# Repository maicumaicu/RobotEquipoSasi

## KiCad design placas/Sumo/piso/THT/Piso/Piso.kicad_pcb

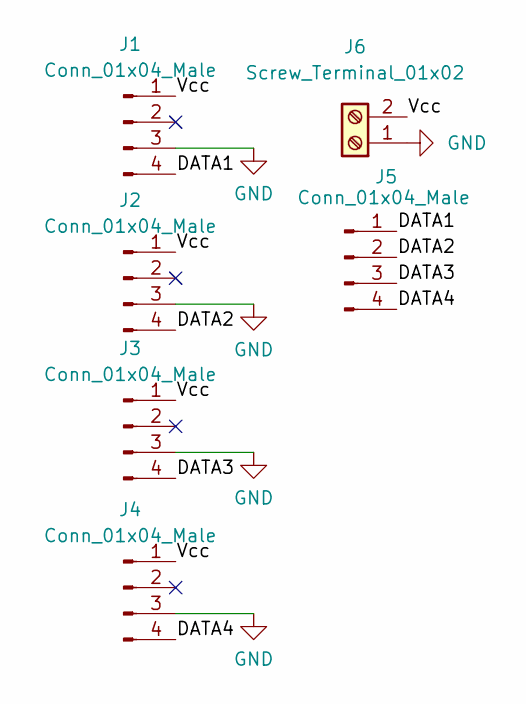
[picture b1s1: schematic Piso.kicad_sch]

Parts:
J1, J2, J3, J4, J5: Conn_01x04_Male; PinHeader_1x04_P2.54mm_Horizontal
J6: Screw_Terminal_01x02; TerminalBlock_bornier-2_P5.08mm

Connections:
/DATA1: J1.4, J5.1
/DATA2: J2.4, J5.2
/DATA3: J3.4, J5.3
/DATA4: J4.4, J5.4
/Vcc: J1.1, J2.1, J3.1, J4.1, J6.2
GND: J1.3, J2.3, J3.3, J4.3, J6.1

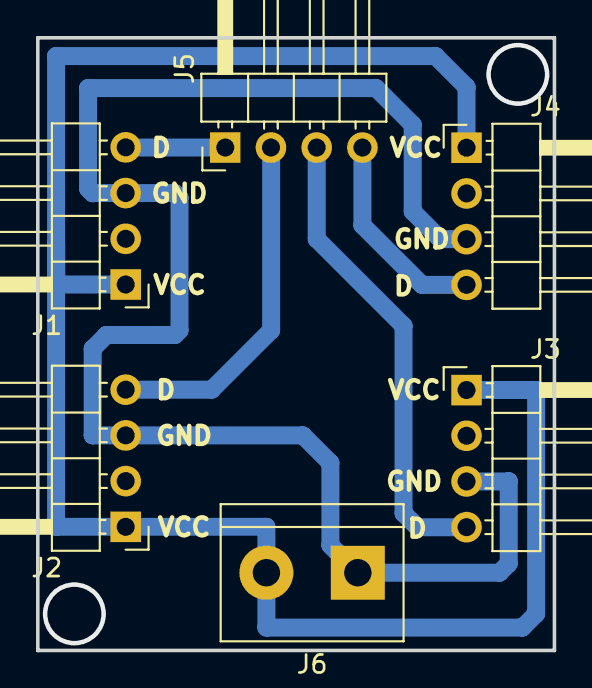
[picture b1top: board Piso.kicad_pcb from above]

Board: 2 copper layers, 28.7 x 34.0 mm, 6 parts (0 on the bottom side), 6 nets.

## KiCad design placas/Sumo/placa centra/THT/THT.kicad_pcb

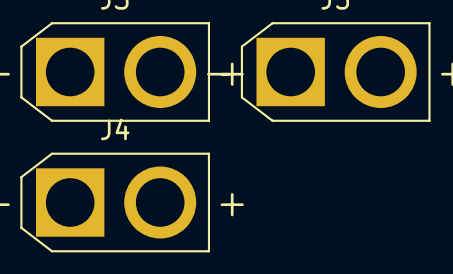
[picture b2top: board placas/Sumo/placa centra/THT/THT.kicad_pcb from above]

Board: 2 copper layers, 3 parts (0 on the bottom side), 2 nets, no tracks yet.

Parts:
J3: BATERIA; AMASS_XT30U-F_1x02_P5.0mm_Vertical
J4: MOTORES; AMASS_XT30U-F_1x02_P5.0mm_Vertical
J5: SENSORES; AMASS_XT30U-F_1x02_P5.0mm_Vertical

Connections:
/GND: J3.1, J4.1, J5.1
/VCC: J3.2, J4.2, J5.2

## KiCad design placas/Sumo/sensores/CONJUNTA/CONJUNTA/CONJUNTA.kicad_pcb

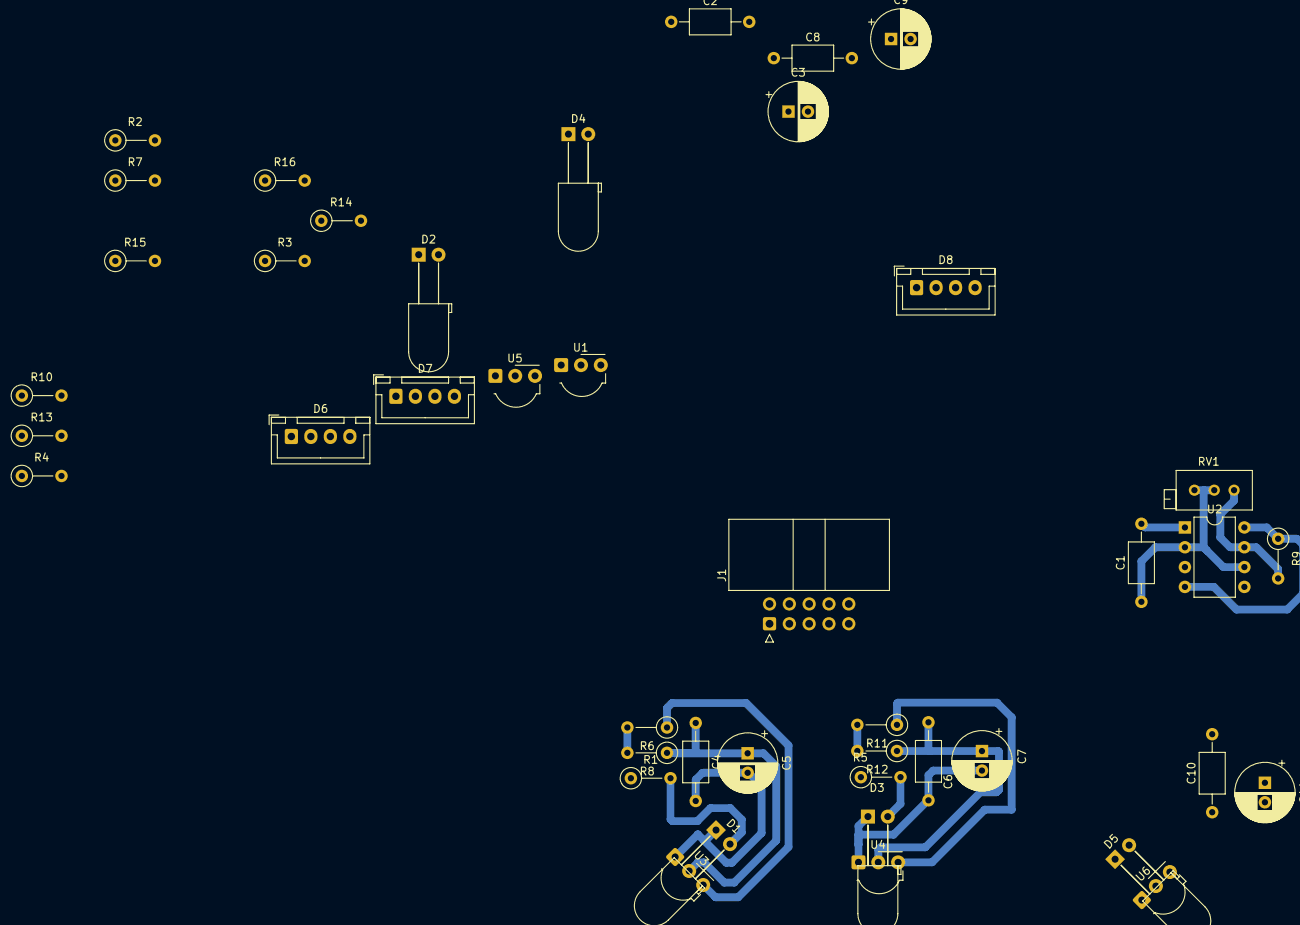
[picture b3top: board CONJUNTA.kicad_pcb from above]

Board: 2 copper layers, 43 parts (0 on the bottom side), 24 nets.

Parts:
C1, C2, C4, C6, C8, C10: 102; C_Axial_L5.1mm_D3.1mm_P10.00mm_Horizontal
C3, C5, C7, C9, C11: 104; CP_Radial_D7.5mm_P2.50mm
D1, D2, D3, D4, D5: LED; LED_D5.0mm_Horizontal_O6.35mm_Z3.0mm
D6, D7, D8: Conn_01x04_Male; JST_XH_B4B-XH-A_1x04_P2.50mm_Vertical
J1: Control Sensores; IDC-Header_2x05_P2.54mm_Horizontal
R1, R4, R5, R7, R10: 220; R_Axial_DIN0207_L6.3mm_D2.5mm_P5.08mm_Vertical
R2, R6, R11, R13, R15: 20k; R_Axial_DIN0207_L6.3mm_D2.5mm_P5.08mm_Vertical
R3, R8, R12, R14, R16: 100; R_Axial_DIN0207_L6.3mm_D2.5mm_P5.08mm_Vertical
R9: 1k8; R_Axial_DIN0207_L6.3mm_D2.5mm_P5.08mm_Vertical
RV1: R_Potentiometer; Potentiometer_Bourns_3296X_Horizontal
U1, U3, U4, U5, U6: TSOP17xx; Vishay_MOLD-3Pin
U2: LM555xN; DIP-8_W7.62mm

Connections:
/5v: D6.4, D7.4, D8.4, J1.1, R2.2, R3.2, R6.2, R8.2, R9.1, R11.2, R12.2, R13.2, R14.2, R15.2, R16.2, U2.4 (R), U2.8 (VCC)
/S1: J1.9, R15.1, U6.3 (OUT)
/S2: J1.7, R13.1, U5.3 (OUT)
/S3: J1.5, R11.1, U4.3 (OUT)
/S4: J1.3, R6.1, U3.3 (OUT)
/S5: J1.10, R2.1, U1.3 (OUT)
/S6: D6.3, J1.8
/S7: D7.3, J1.6
/S8: D8.3, J1.4
/gnd: D6.2, D7.2, D8.2
GND: C1.2, C2.2, C3.2, C4.2, C5.2, C6.2, C7.2, C8.2, C9.2, C10.2, C11.2, D1.1 (K), D2.1 (K), D3.1 (K), D4.1 (K), D5.1 (K), J1.2, U1.1 (GND), U2.1 (GND), U3.1 (GND), U4.1 (GND), U5.1 (GND), U6.1 (GND)
unnamed: C1.1, RV1.2, RV1.3, U2.2 (TR), U2.6 (THR)
unnamed: C2.1, C3.1, R3.1, U1.2 (Vs)
unnamed: C4.1, C5.1, R8.1, U3.2 (Vs)
unnamed: C6.1, C7.1, R12.1, U4.2 (Vs)
unnamed: C8.1, C9.1, R14.1, U5.2 (Vs)
unnamed: C10.1, C11.1, R16.1, U6.2 (Vs)
unnamed: D1.2 (A), R1.2
unnamed: D2.2 (A), R4.2
unnamed: D3.2 (A), R5.2
unnamed: D4.2 (A), R7.2
unnamed: D5.2 (A), R10.2
unnamed: D6.1, D7.1, D8.1, R1.1, R4.1, R5.1, R7.1, R10.1, U2.3 (Q)
unnamed: R9.2, RV1.1, U2.7 (DIS)

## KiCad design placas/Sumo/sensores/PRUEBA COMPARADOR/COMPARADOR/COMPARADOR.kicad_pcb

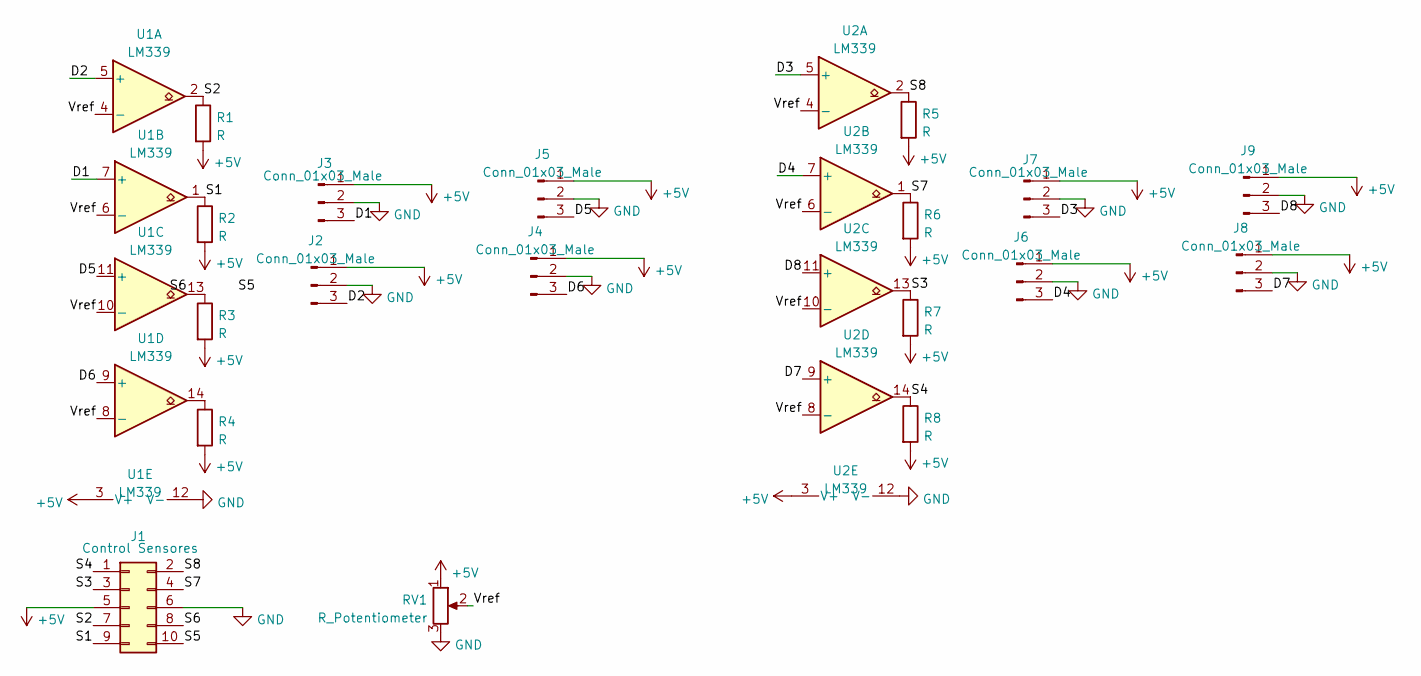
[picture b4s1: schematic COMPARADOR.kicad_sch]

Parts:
J1: Control Sensores; IDC-Header_2x05_P2.54mm_Horizontal
J2, J3, J4, J5, J6, J7, J8, J9: Conn_01x03_Male; PinHeader_1x03_P2.54mm_Vertical
R1, R2, R3, R4, R5, R6, R7, R8: R; R_Axial_DIN0207_L6.3mm_D2.5mm_P10.16mm_Horizontal
RV1: R_Potentiometer; Potentiometer_Bourns_3299W_Vertical
U1, U2: LM339; DIP-14_W7.62mm_Socket_LongPads

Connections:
+5V: J1.5, J2.1, J3.1, J4.1, J5.1, J6.1, J7.1, J8.1, J9.1, R1.2, R2.2, R3.2, R4.2, R5.2, R6.2, R7.2, R8.2, RV1.1, U1.3 (V+), U2.3 (V+)
/D1: J3.3, U1.7 (+)
/D2: J2.3, U1.5 (+)
/D3: J7.3, U2.5 (+)
/D4: J6.3, U2.7 (+)
/D5: J5.3, U1.11 (+)
/D6: J4.3, U1.9 (+)
/D7: J8.3, U2.9 (+)
/D8: J9.3, U2.11 (+)
/S1: J1.9, R2.1, U1.1
/S2: J1.7, R1.1, U1.2
/S3: J1.3, R7.1, U2.13
/S4: J1.1, R8.1, U2.14
/S5: J1.10
/S6: J1.8
/S7: J1.4, R6.1, U2.1
/S8: J1.2, R5.1, U2.2
/Vref: RV1.2, U1.4 (-), U1.6 (-), U1.8 (-), U1.10 (-), U2.4 (-), U2.6 (-), U2.8 (-), U2.10 (-)
GND: J1.6, J2.2, J3.2, J4.2, J5.2, J6.2, J7.2, J8.2, J9.2, RV1.3, U1.12 (V-), U2.12 (V-)
unnamed: R3.1, U1.13
unnamed: R4.1, U1.14

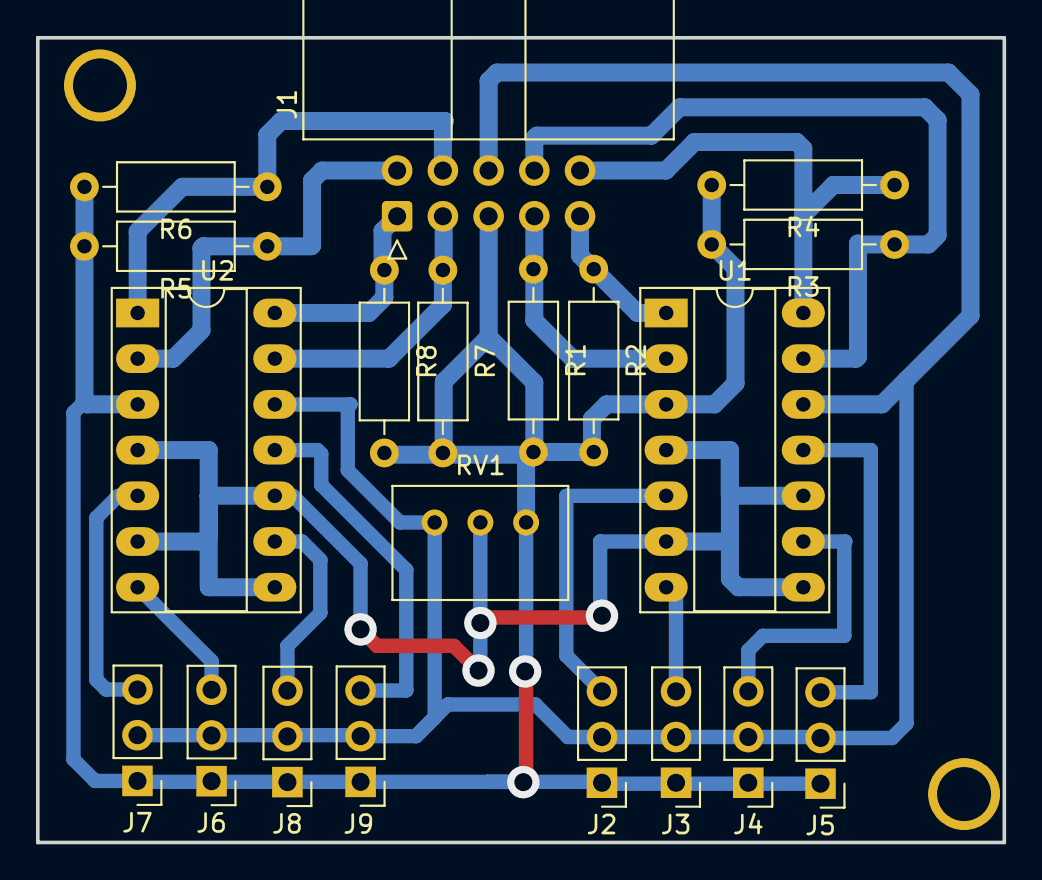
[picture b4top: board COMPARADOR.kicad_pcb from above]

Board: 2 copper layers, 53.7 x 44.7 mm, 20 parts (0 on the bottom side), 19 nets.

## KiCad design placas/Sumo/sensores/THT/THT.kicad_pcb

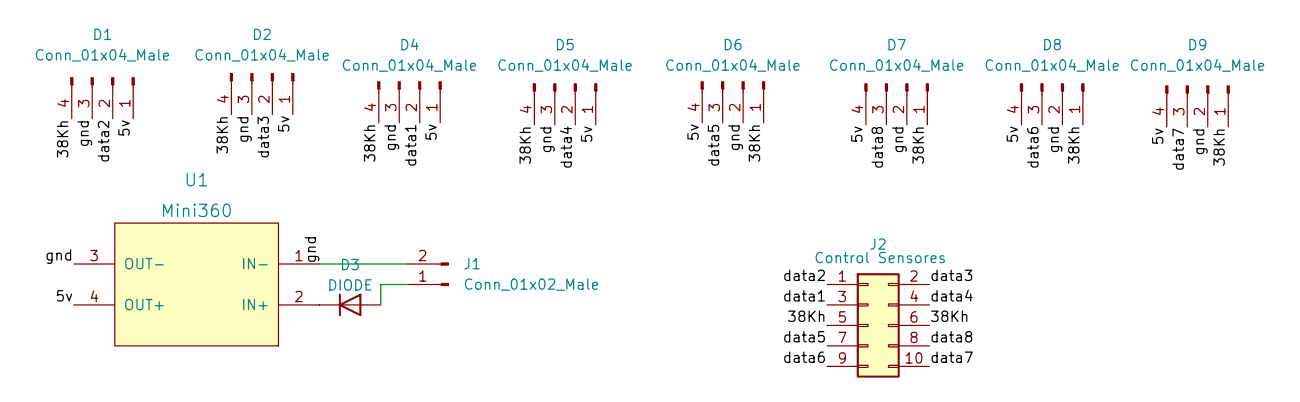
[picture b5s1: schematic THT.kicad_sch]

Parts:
D1, D2, D4, D5, D6, D7, D8, D9: Conn_01x04_Male; PinHeader_1x04_P2.54mm_Horizontal
D3: DIODE; D_5W_P12.70mm_Horizontal
J1: Conn_01x02_Male; TerminalBlock_bornier-2_P5.08mm
J2: Control Sensores; IDC-Header_2x05_P2.54mm_Vertical
U1: Mini360; Mini360_step-down

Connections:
/5v: D1.1, D2.1, D4.1, D5.1, D6.4, D7.4, D8.4, D9.4, U1.4 (OUT+)
/38Kh: D1.4, D2.4, D4.4, D5.4, D6.1, D7.1, D8.1, D9.1, J2.5, J2.6
/data1: D4.2, J2.3
/data2: D1.2, J2.1
/data3: D2.2, J2.2
/data4: D5.2, J2.4
/data5: D6.3, J2.7
/data6: D8.3, J2.9
/data7: D9.3, J2.10
/data8: D7.3, J2.8
/gnd: D1.3, D2.3, D4.3, D5.3, D6.2, D7.2, D8.2, D9.2, J1.2, U1.1 (IN-), U1.3 (OUT-)
unnamed: D3.1 (A), J1.1
unnamed: D3.2 (K), U1.2 (IN+)

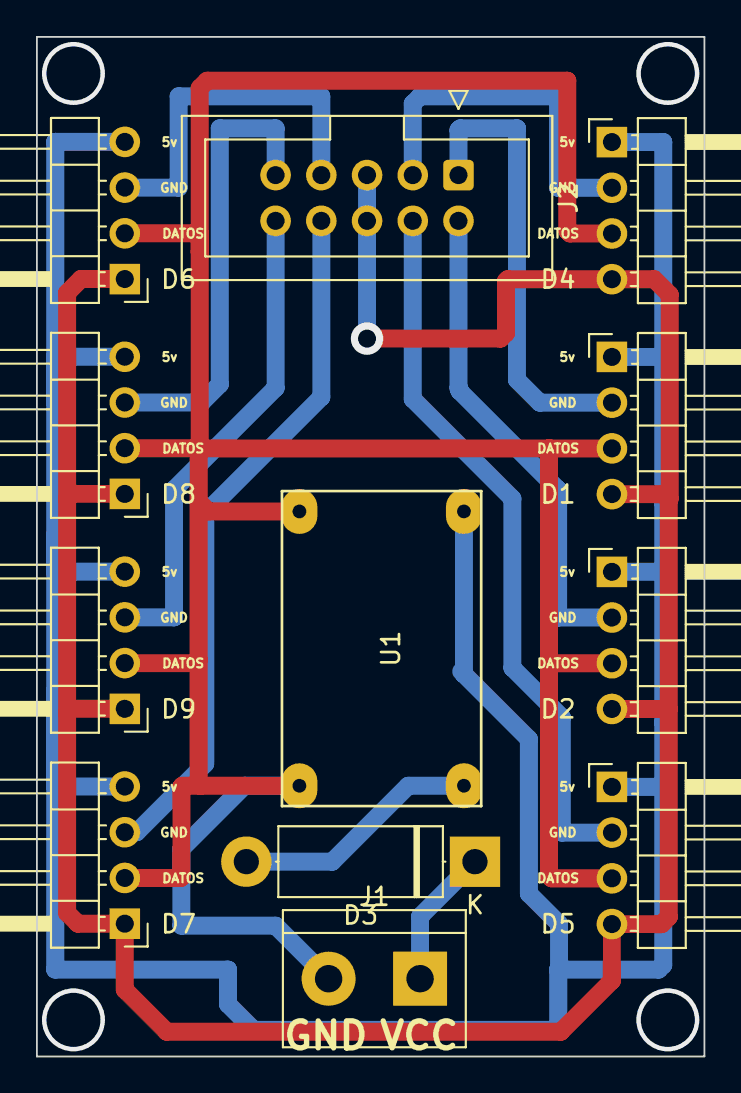
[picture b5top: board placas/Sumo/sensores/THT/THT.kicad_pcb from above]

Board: 2 copper layers, 37.1 x 56.6 mm, 12 parts (0 on the bottom side), 13 nets.

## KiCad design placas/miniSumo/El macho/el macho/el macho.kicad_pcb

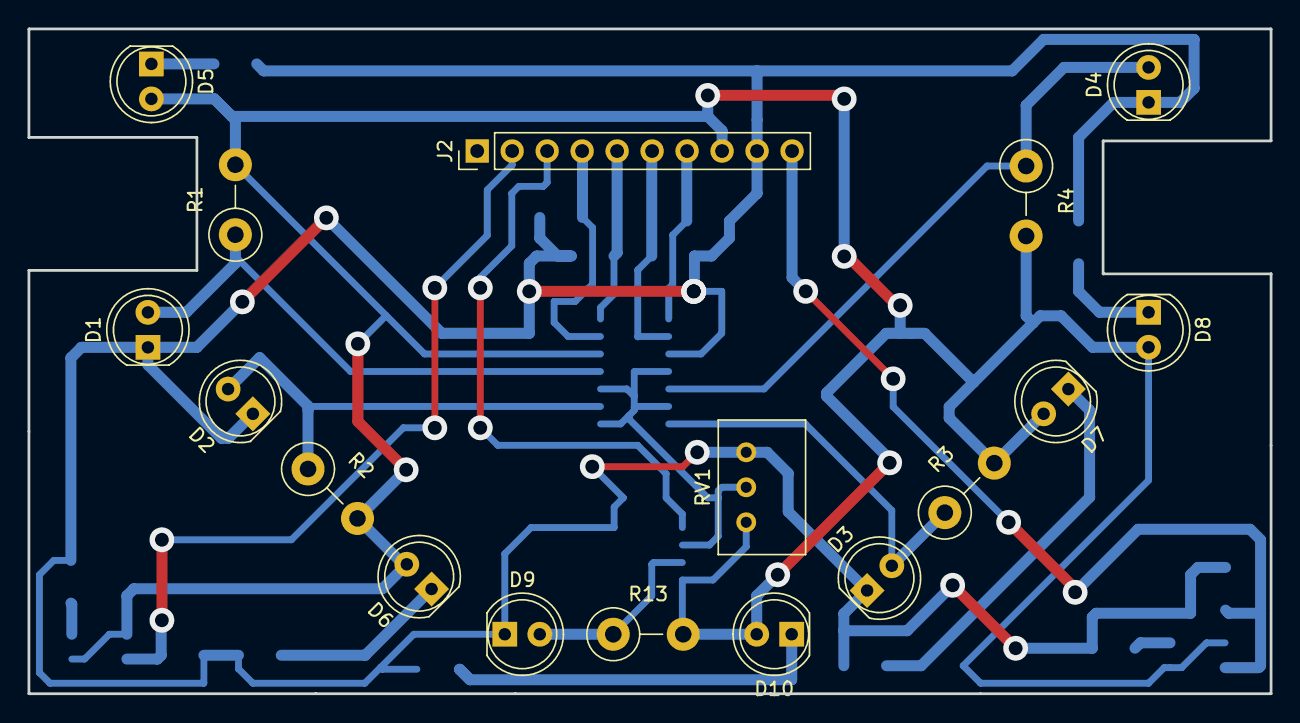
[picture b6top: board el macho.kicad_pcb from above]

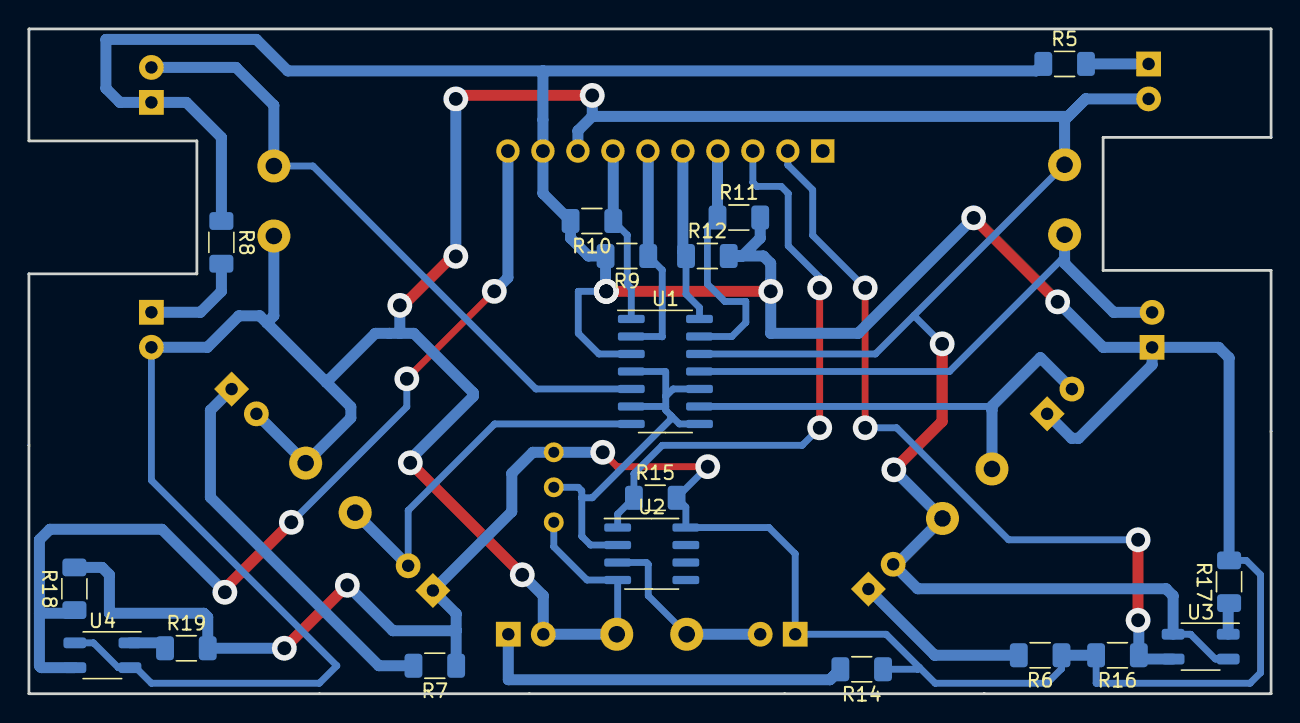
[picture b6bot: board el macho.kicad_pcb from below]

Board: 2 copper layers, 90.2 x 48.3 mm, 35 parts (18 on the bottom side), 22 nets.

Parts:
D1, D2, D3, D4, D9: IR RECEIVER; LED_D5.0mm
D5, D6, D7, D8, D10: IR TRANSMITTER; LED_D5.0mm
J2: Conn_01x10_Pin; PinHeader_1x10_P2.54mm_Vertical
R1, R2, R3, R4, R13: 10k; R_Axial_DIN0411_L9.9mm_D3.6mm_P5.08mm_Vertical
R5, R6, R7, R8, R14: 100; R_1206_3216Metric_Pad1.30x1.75mm_HandSolder
R9, R10, R11, R12, R15: 1k; R_1206_3216Metric_Pad1.30x1.75mm_HandSolder
R16, R18: 47K; R_1206_3216Metric_Pad1.30x1.75mm_HandSolder
R17, R19: 22; R_1206_3216Metric_Pad1.30x1.75mm_HandSolder
RV1: R_Potentiometer; Potentiometer_Bourns_3299W_Vertical
U1: LM339; SO-14_3.9x8.65mm_P1.27mm
U2: LM358; SOIC-8_3.9x4.9mm_P1.27mm
U3, U4: QRE1113GR; OnSemi_CASE100CY

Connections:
+5V: D1.1 (K), D2.1 (K), D3.1 (K), D4.1 (K), D9.1 (K), J2.9, R5.1, R6.1, R7.1, R8.1, R9.2, R10.2, R11.2, R12.2, R14.1, R15.2, R16.2, R17.2, R18.2, R19.2, RV1.1, U1.3 (V+), U2.8 (V+)
/D1: D4.2 (A), R4.1, U1.5 (+)
/D2: D3.2 (A), R3.1, U1.7 (+)
/D3: D2.2 (A), R2.1, U1.9 (+)
/D4: D1.2 (A), R1.1, U1.11 (+)
/D5: D9.2 (A), R13.1, U2.3 (+)
/SIGNAL1: J2.2, R16.1, U3.3
/SIGNAL2: J2.10, R18.1, U4.3
GND: D5.2 (A), D6.2 (A), D7.2 (A), D8.2 (A), D10.2 (A), J2.8, R1.2, R2.2, R3.2, R4.2, R13.2, RV1.3, U1.12 (V-), U2.4 (V-), U3.2 (K), U3.4, U4.2 (K), U4.4
unnamed: D5.1 (K), R5.2
unnamed: D6.1 (K), R6.2
unnamed: D7.1 (K), R7.2
unnamed: D8.1 (K), R8.2
unnamed: D10.1 (K), R14.2
unnamed: J2.3, R15.1, U2.1
unnamed: J2.4, R11.1, U1.13
unnamed: J2.5, R12.1, U1.14
unnamed: J2.6, R9.1, U1.2
unnamed: J2.7, R10.1, U1.1
unnamed: RV1.2, U1.4 (-), U1.6 (-), U1.8 (-), U1.10 (-), U2.2 (-)
unnamed: R17.1, U3.1 (A)
unnamed: R19.1, U4.1 (A)

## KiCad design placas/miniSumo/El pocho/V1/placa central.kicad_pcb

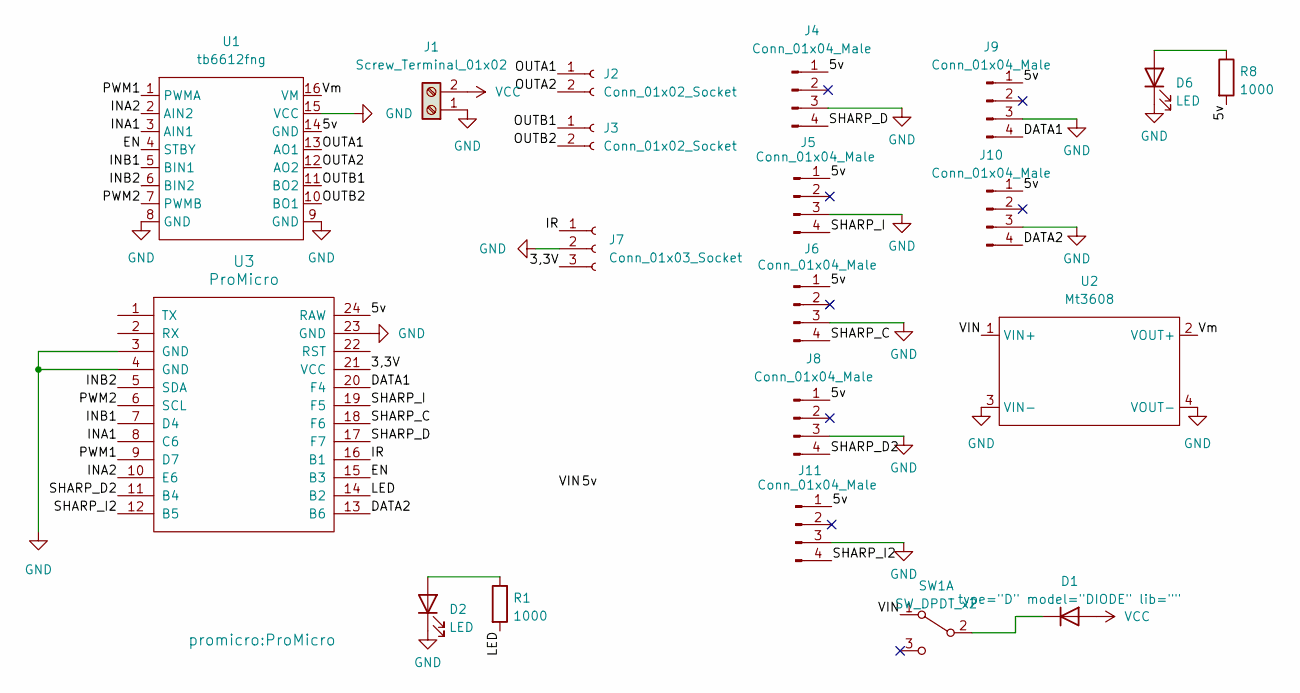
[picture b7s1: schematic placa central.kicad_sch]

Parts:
D1: type="D" model="DIODE" lib=""; D_5W_P5.08mm_Vertical_AnodeUp
D2, D6: LED; LED_D3.0mm_FlatTop
J1: Screw_Terminal_01x02; PinSocket_1x02_P2.54mm_Vertical
J2, J3: Conn_01x02_Socket; PinSocket_1x02_P2.54mm_Vertical
J4, J5, J6, J8, J9, J10, J11: Conn_01x04_Male; PinHeader_1x04_P2.54mm_Vertical
J7: Conn_01x03_Socket; PinSocket_1x03_P2.54mm_Vertical
R1, R8: 1000; R_1210_3225Metric
SW1: SW_DPDT_x2; SW_Slide_1P2T_CK_OS102011MS2Q
U1: tb6612fng
U2: Mt3608; Sx1308
U3: ProMicro

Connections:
/3,3V: J7.3, U3.21 (VCC)
/5v: J4.1, J5.1, J6.1, J8.1, J9.1, J10.1, J11.1, R8.2, SW1.1 (A), U1.14 (GND), U2.1 (VIN+), U3.24 (RAW)
/DATA1: J9.4, U3.20 (F4)
/DATA2: J10.4, U3.13 (B6)
/EN: U1.4 (STBY), U3.15 (B3)
/INA1: U1.3 (AIN1), U3.8 (C6)
/INA2: U1.2 (AIN2), U3.10 (E6)
/INB1: U1.5 (BIN1), U3.7 (D4)
/INB2: U1.6 (BIN2), U3.5 (SDA)
/IR: J7.1, U3.16 (B1)
/LED: R1.2, U3.14 (B2)
/OUTA1: J2.1, U1.13 (AO1)
/OUTA2: J2.2, U1.12 (AO2)
/OUTB1: J3.1, U1.11 (BO2)
/OUTB2: J3.2, U1.10 (BO1)
/PWM1: U1.1 (PWMA), U3.9 (D7)
/PWM2: U1.7 (PWMB), U3.6 (SCL)
/SHARP_C: J6.4, U3.18 (F6)
/SHARP_D: J4.4, U3.17 (F7)
/SHARP_D2: J8.4, U3.11 (B4)
/SHARP_I: J5.4, U3.19 (F5)
/SHARP_I2: J11.4, U3.12 (B5)
/Vm: U1.16 (VM), U2.2 (VOUT+)
GND: D2.1 (K), D6.1 (K), J1.1, J4.3, J5.3, J6.3, J7.2, J8.3, J9.3, J10.3, J11.3, U1.8 (GND), U1.9 (GND), U1.15 (VCC), U2.3 (VIN-), U2.4 (VOUT-), U3.3 (GND), U3.4 (GND), U3.23 (GND)
unnamed: D1.2 (K), SW1.2 (B)
unnamed: D2.2 (A), R1.1
unnamed: D6.2 (A), R8.1
VCC: D1.1 (A), J1.2

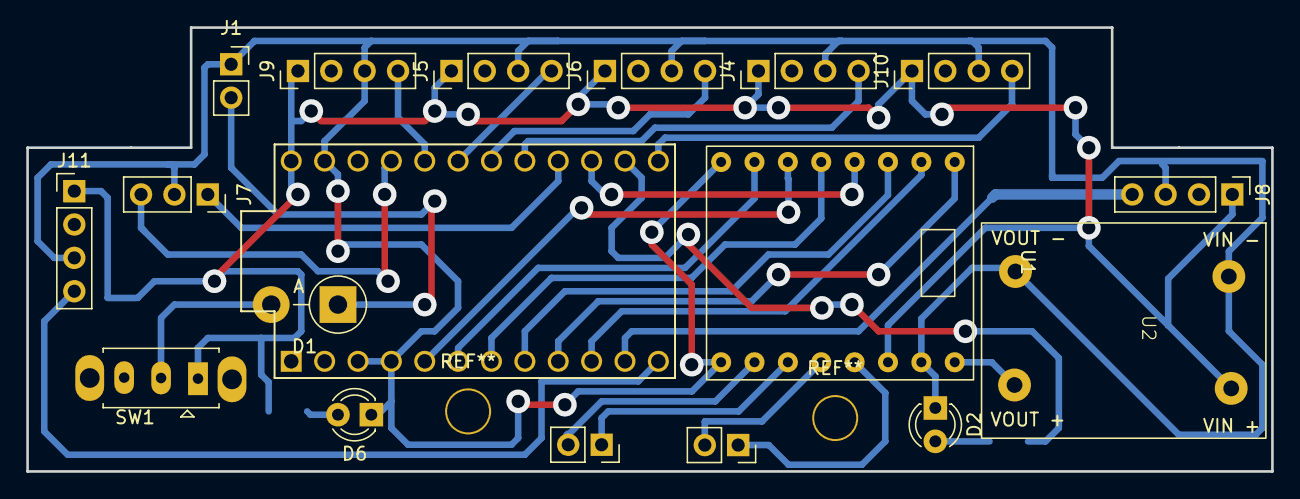
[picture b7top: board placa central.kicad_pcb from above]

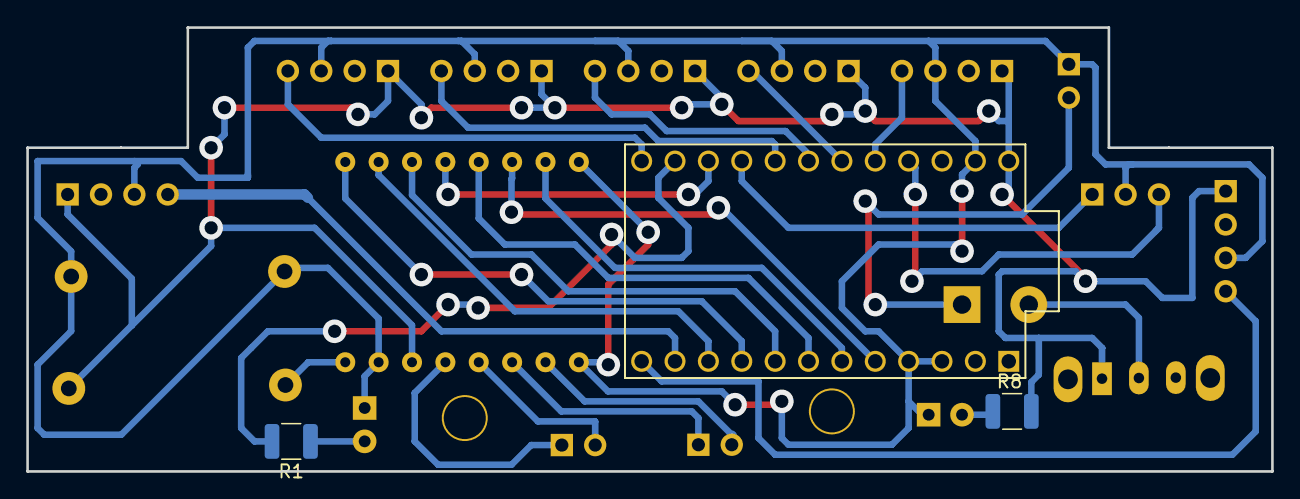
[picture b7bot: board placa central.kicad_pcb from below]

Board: 2 copper layers, 94.7 x 33.8 mm, 20 parts (2 on the bottom side), 28 nets.

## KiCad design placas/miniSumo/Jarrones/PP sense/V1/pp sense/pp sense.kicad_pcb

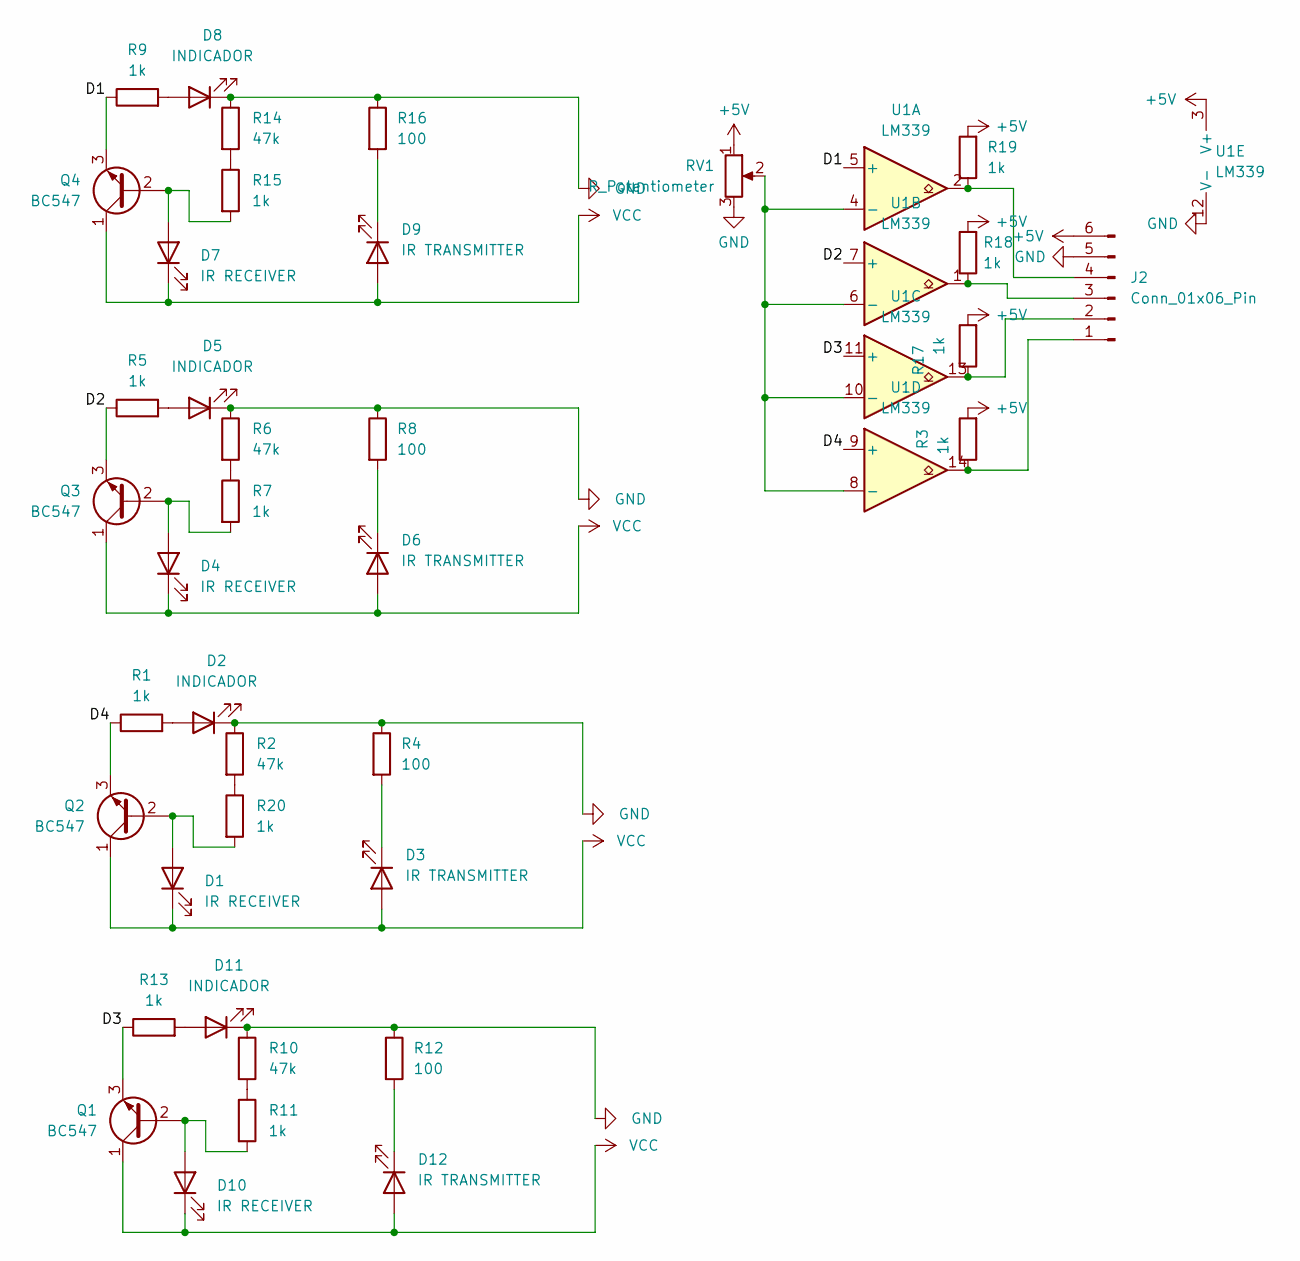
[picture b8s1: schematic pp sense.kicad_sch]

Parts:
D1, D4, D7, D10: IR RECEIVER; LED_D5.0mm
D2, D5, D8, D11: INDICADOR; LED_1206_3216Metric_Pad1.42x1.75mm_HandSolder
D3, D6, D9, D12: IR TRANSMITTER; LED_D5.0mm
J2: Conn_01x06_Pin; PinHeader_1x06_P2.54mm_Vertical
Q1, Q2, Q3, Q4: BC547; TO-92_Inline
R1, R3, R5, R7, R9, R11, R13, R15, R17, R18, R19, R20: 1k; R_1206_3216Metric_Pad1.30x1.75mm_HandSolder
R2, R6, R10, R14: 47k; R_1206_3216Metric_Pad1.30x1.75mm_HandSolder
R4, R8, R12, R16: 100; R_1206_3216Metric_Pad1.30x1.75mm_HandSolder
RV1: R_Potentiometer; Potentiometer_Bourns_3299W_Vertical
U1: LM339; DIP-14_W7.62mm

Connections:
+5V: J2.6, R3.2, R17.2, R18.2, R19.2, RV1.1, U1.3 (V+)
/D1: Q4.3 (E), R9.1, U1.5 (+)
/D2: Q3.3 (E), R5.1, U1.7 (+)
/D3: Q1.3 (E), R13.1, U1.11 (+)
/D4: Q2.3 (E), R1.1, U1.9 (+)
GND: D2.1 (K), D5.1 (K), D8.1 (K), D11.1 (K), J2.5, R2.1, R4.1, R6.1, R8.1, R10.1, R12.1, R14.1, R16.1, RV1.3, U1.12 (V-)
unnamed: D1.2 (A), Q2.2 (B), R20.2
unnamed: D2.2 (A), R1.2
unnamed: D3.1 (K), R4.2
unnamed: D4.2 (A), Q3.2 (B), R7.2
unnamed: D5.2 (A), R5.2
unnamed: D6.1 (K), R8.2
unnamed: D7.2 (A), Q4.2 (B), R15.2
unnamed: D8.2 (A), R9.2
unnamed: D9.1 (K), R16.2
unnamed: D10.2 (A), Q1.2 (B), R11.2
unnamed: D11.2 (A), R13.2
unnamed: D12.1 (K), R12.2
unnamed: J2.1, R3.1, U1.14
unnamed: J2.2, R17.1, U1.13
unnamed: J2.3, R18.1, U1.1
unnamed: J2.4, R19.1, U1.2
unnamed: R2.2, R20.1
unnamed: R6.2, R7.1
unnamed: R10.2, R11.1
unnamed: R14.2, R15.1
unnamed: RV1.2, U1.4 (-), U1.6 (-), U1.8 (-), U1.10 (-)
VCC: D1.1 (K), D3.2 (A), D4.1 (K), D6.2 (A), D7.1 (K), D9.2 (A), D10.1 (K), D12.2 (A), Q1.1 (C), Q2.1 (C), Q3.1 (C), Q4.1 (C)

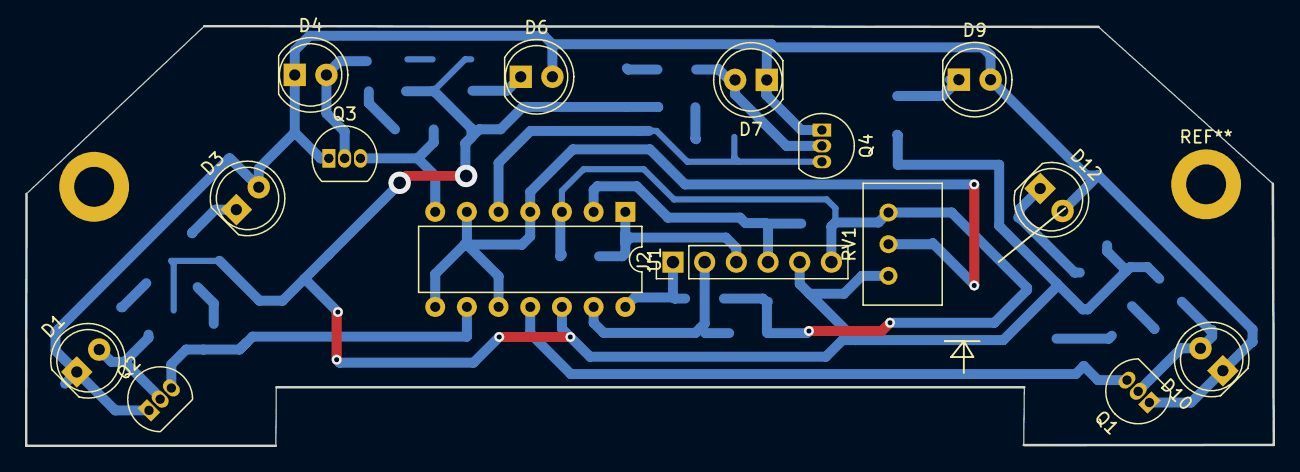
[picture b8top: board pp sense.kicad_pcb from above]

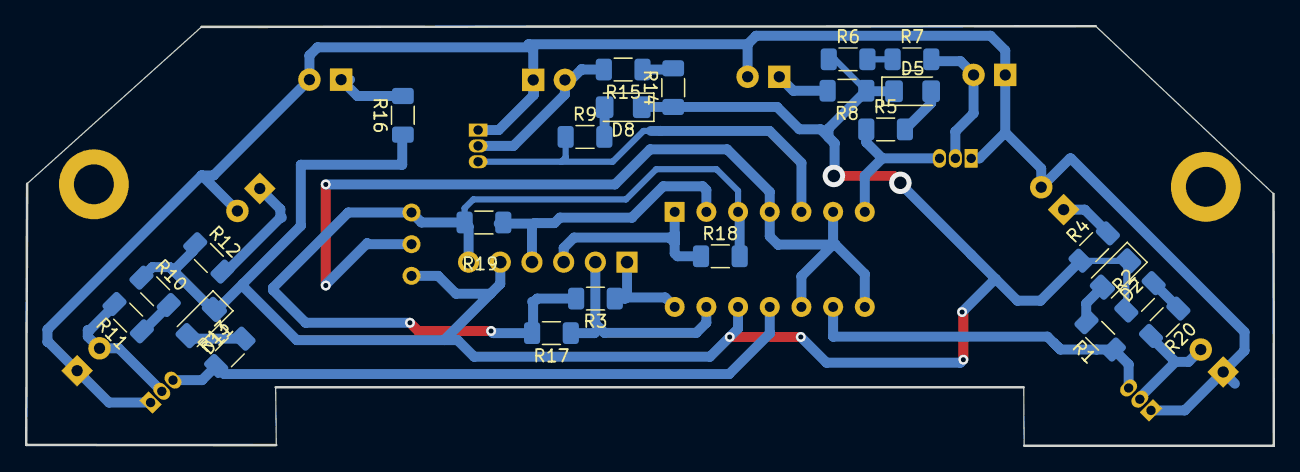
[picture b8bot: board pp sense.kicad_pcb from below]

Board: 2 copper layers, 100.0 x 33.6 mm, 39 parts (24 on the bottom side), 28 nets.
